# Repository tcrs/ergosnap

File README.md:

# ErgoSnap Keyboard

WARNING. This is rev1.1, which works fine but has a few issues:

 - The silkscreen for the ProMicro outline is incorrect for the USB-up placement
 - USB cable only just plugs into the ProMicro on the left half (plug shroud is
   against the edge of the PCB below the ProMicro)
 - SDA & SCL are the wrong way around on the 5pin header for the Pimoroni
   trackball breakout, so that doesn't work without some jumper wires...

[ErgoDash][1] layout with [Mitosis][2] style PCB construction, reversible ProMicro
chin from [Ergo42][3].

 - Removed all the wiring for backlight/underlight LEDs
 - Uses through-switch diode holes
 - M6 mouting holes on the "inside" board edges for tenting
 - 5 pin connector for [trackball module][4] (no software yet...)

[1]: https://github.com/omkbd/ErgoDash
[2]: https://github.com/reversebias/mitosis-hardware
[3]: https://github.com/Biacco42/Ergo42
[4]: https://shop.pimoroni.com/products/trackball-breakout

## Fabrication

I got my PCBS made at [JLCPCB][5]. No issues.

[5]: https://jlcpcb.com/

## BOM

 - 4 x PCBs
 - 68 x Keyswitches (Cherry MX or compatible)
 - 68 x Diodes (1N4148)
 - 2 x ProMicro + header pins 
 - 2 x TRRS jacks (PJ-320A [aliexpress](https://www.aliexpress.com/item/32825553898.html))
 - 1 x TRRS cable
 - 2 x 4k7 Ohm resistors (I2C pullups)
 - 2 x 5pin headers
 - 4 x M6 nylon screw thread + nuts (for tenting, optional)
 - Some sticky-backed neoprene tape (for padding/non-slip on the bottom of the
   board)

## Build

See [build guide](build_guide/).

## Software

[QMK](https://qmk.fm/). ErgoSnap uses exactly the same matrix as the ErgoDash,
so just build an ErgoDash layout (using the `LAYOUT_3key_1us` layout type).

For an example see my [`ergodash-isolike` layout](https://github.com/tcrs/qmk_firmware/tree/ergosnap-isolike).

Example make command:

	make ergodash/rev1:isolike:avrdude

## License

ErgoDash & Ergo42 are MIT, Mitosis is GPLv3. So this work as a whole is GPLv3.

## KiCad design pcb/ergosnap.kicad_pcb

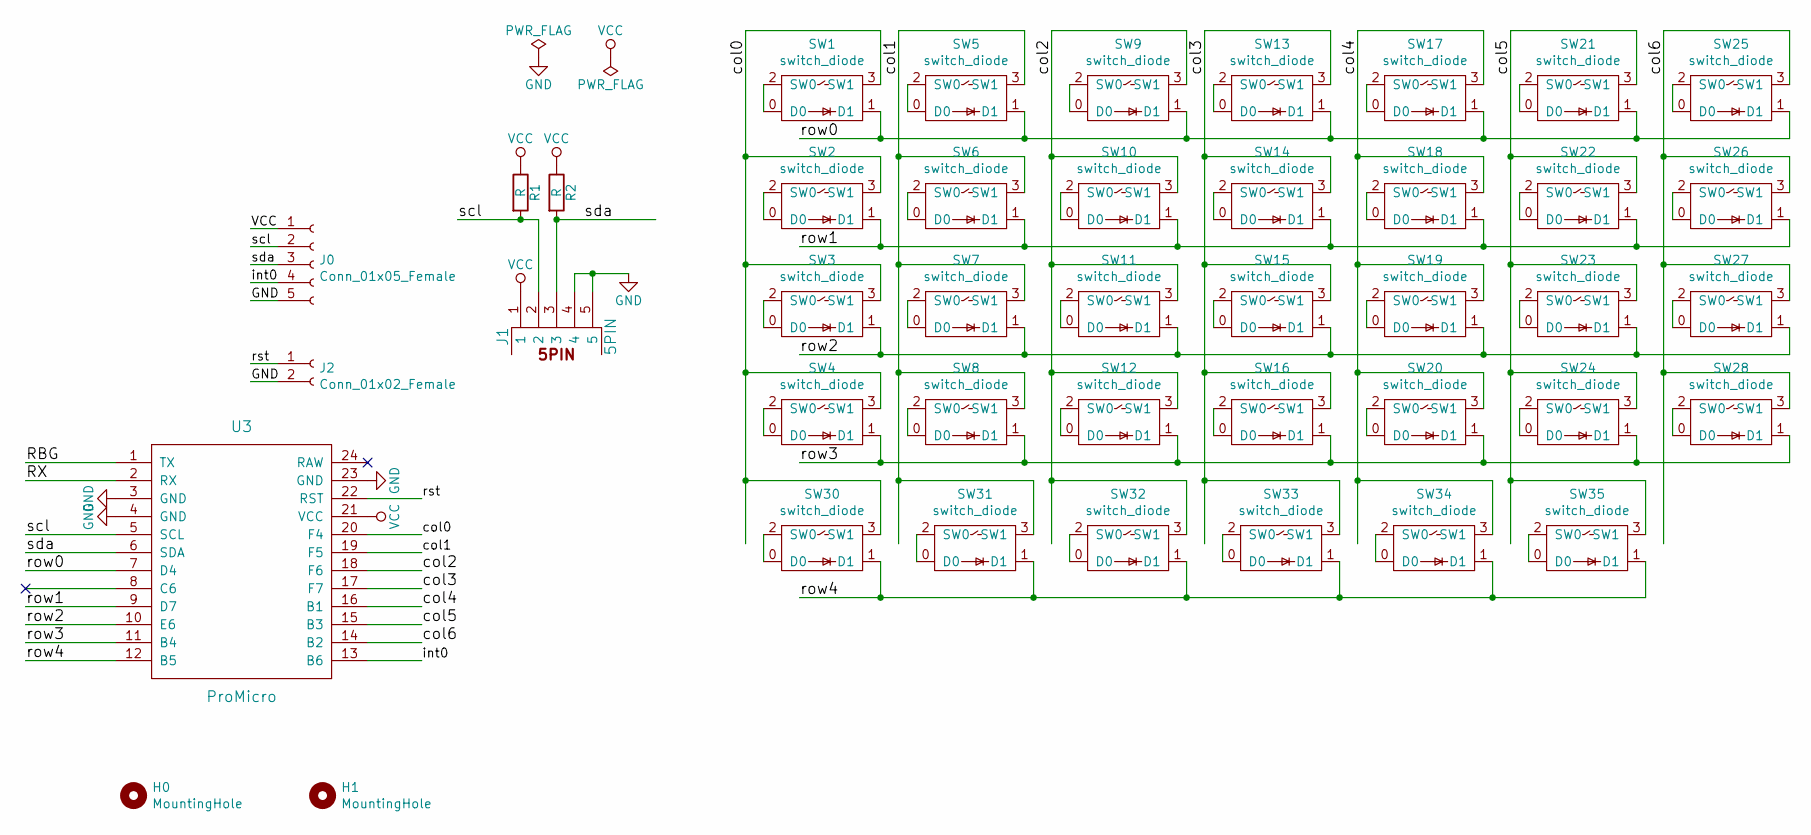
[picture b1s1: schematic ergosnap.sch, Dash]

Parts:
H0, H1: MountingHole; MountingHole_6.4mm_M6
J0: Conn_01x05_Female; pimoroni_trackball
J1: 5PIN; trrs_jack
J2: Conn_01x02_Female; SolderWirePad_1x02_P3.81mm_Drill0.8mm
R1, R2: R; R_Axial_DIN0207_L6.3mm_D2.5mm_P10.16mm_Horizontal
SW1, SW2, SW3, SW4, SW5, SW6, SW7, SW8, SW9, SW10, SW11, SW12, SW13, SW14, SW15, SW16, SW17, SW18, SW19, SW20, SW21, SW22, SW23, SW24, SW25, SW26, SW27, SW28, SW30, SW31, SW32, SW33, SW34, SW35: switch_diode; cherry_mx_diode_snapout
U3: ProMicro; ProMicroReversible

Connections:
/RBG: U3.1 (TX)
/RX: U3.2 (RX)
/col0: SW1.3 (SW1), SW2.3 (SW1), SW3.3 (SW1), SW4.3 (SW1), SW30.3 (SW1), U3.20 (F4)
/col1: SW5.3 (SW1), SW6.3 (SW1), SW7.3 (SW1), SW8.3 (SW1), SW31.3 (SW1), U3.19 (F5)
/col2: SW9.3 (SW1), SW10.3 (SW1), SW11.3 (SW1), SW12.3 (SW1), SW32.3 (SW1), U3.18 (F6)
/col3: SW13.3 (SW1), SW14.3 (SW1), SW15.3 (SW1), SW16.3 (SW1), SW33.3 (SW1), U3.17 (F7)
/col4: SW17.3 (SW1), SW18.3 (SW1), SW19.3 (SW1), SW20.3 (SW1), SW34.3 (SW1), U3.16 (B1)
/col5: SW21.3 (SW1), SW22.3 (SW1), SW23.3 (SW1), SW24.3 (SW1), SW35.3 (SW1), U3.15 (B3)
/col6: SW25.3 (SW1), SW26.3 (SW1), SW27.3 (SW1), SW28.3 (SW1), U3.14 (B2)
/int0: J0.4, U3.13 (B6)
/row0: SW1.1 (D1), SW5.1 (D1), SW9.1 (D1), SW13.1 (D1), SW17.1 (D1), SW21.1 (D1), SW25.1 (D1), U3.7 (D4)
/row1: SW2.1 (D1), SW6.1 (D1), SW10.1 (D1), SW14.1 (D1), SW18.1 (D1), SW22.1 (D1), SW26.1 (D1), U3.9 (D7)
/row2: SW3.1 (D1), SW7.1 (D1), SW11.1 (D1), SW15.1 (D1), SW19.1 (D1), SW23.1 (D1), SW27.1 (D1), U3.10 (E6)
/row3: SW4.1 (D1), SW8.1 (D1), SW12.1 (D1), SW16.1 (D1), SW20.1 (D1), SW24.1 (D1), SW28.1 (D1), U3.11 (B4)
/row4: SW30.1 (D1), SW31.1 (D1), SW32.1 (D1), SW33.1 (D1), SW34.1 (D1), SW35.1 (D1), U3.12 (B5)
/rst: J2.1, U3.22 (RST)
/scl: J0.2, J1.2, R1.2, U3.5 (SCL)
/sda: J0.3, J1.3, R2.2, U3.6 (SDA)
GND: J0.5, J1.4, J1.5, J2.2, U3.3 (GND), U3.4 (GND), U3.23 (GND)
unnamed: SW1.0 (D0), SW1.2 (SW0)
unnamed: SW2.0 (D0), SW2.2 (SW0)
unnamed: SW3.0 (D0), SW3.2 (SW0)
unnamed: SW4.0 (D0), SW4.2 (SW0)
unnamed: SW5.0 (D0), SW5.2 (SW0)
unnamed: SW6.0 (D0), SW6.2 (SW0)
unnamed: SW7.0 (D0), SW7.2 (SW0)
unnamed: SW8.0 (D0), SW8.2 (SW0)
unnamed: SW9.0 (D0), SW9.2 (SW0)
unnamed: SW10.0 (D0), SW10.2 (SW0)
unnamed: SW11.0 (D0), SW11.2 (SW0)
unnamed: SW12.0 (D0), SW12.2 (SW0)
unnamed: SW13.0 (D0), SW13.2 (SW0)
unnamed: SW14.0 (D0), SW14.2 (SW0)
unnamed: SW15.0 (D0), SW15.2 (SW0)
unnamed: SW16.0 (D0), SW16.2 (SW0)
unnamed: SW17.0 (D0), SW17.2 (SW0)
unnamed: SW18.0 (D0), SW18.2 (SW0)
unnamed: SW19.0 (D0), SW19.2 (SW0)
unnamed: SW20.0 (D0), SW20.2 (SW0)
unnamed: SW21.0 (D0), SW21.2 (SW0)
unnamed: SW22.0 (D0), SW22.2 (SW0)
unnamed: SW23.0 (D0), SW23.2 (SW0)
unnamed: SW24.0 (D0), SW24.2 (SW0)
unnamed: SW25.0 (D0), SW25.2 (SW0)
unnamed: SW26.0 (D0), SW26.2 (SW0)
unnamed: SW27.0 (D0), SW27.2 (SW0)
unnamed: SW28.0 (D0), SW28.2 (SW0)
unnamed: SW30.0 (D0), SW30.2 (SW0)
unnamed: SW31.0 (D0), SW31.2 (SW0)
unnamed: SW32.0 (D0), SW32.2 (SW0)
unnamed: SW33.0 (D0), SW33.2 (SW0)
unnamed: SW34.0 (D0), SW34.2 (SW0)
unnamed: SW35.0 (D0), SW35.2 (SW0)
VCC: J0.1, J1.1, R1.1, R2.1, U3.21 (VCC)

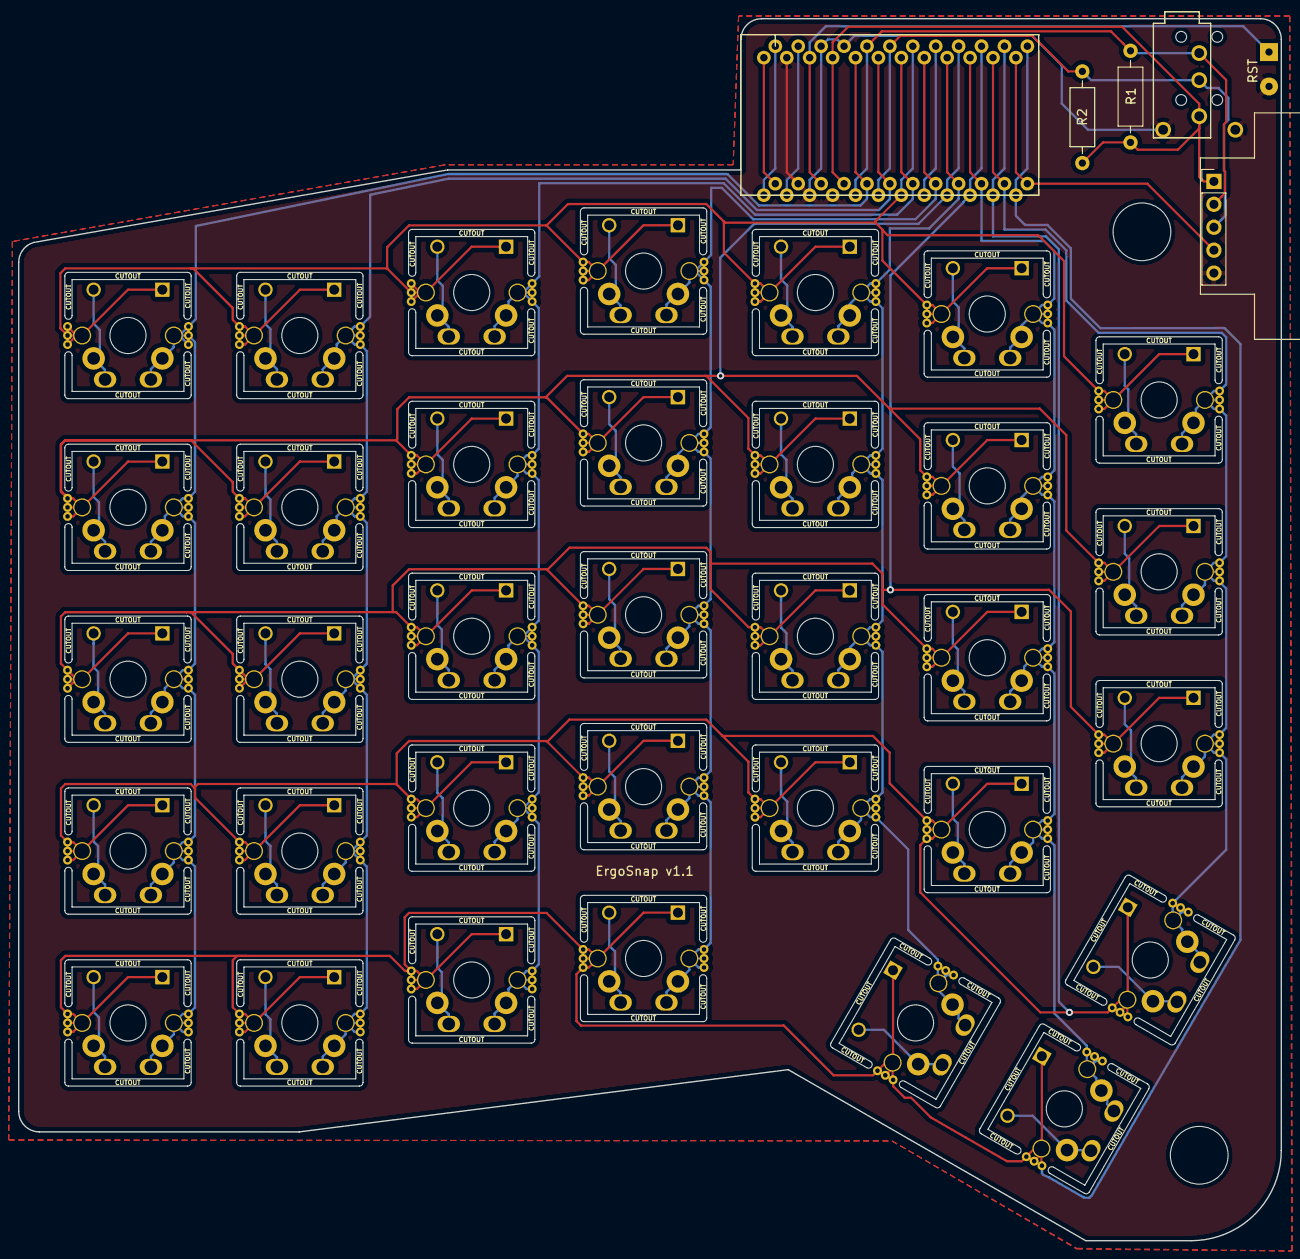
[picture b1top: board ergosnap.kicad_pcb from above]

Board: 2 copper layers, 140.0 x 135.5 mm, 42 parts (0 on the bottom side), 52 nets.

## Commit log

2019-07-08 Initial version of PCB
2019-07-08 Fiddle with trackball header
2019-07-09 Add cutout on silkscreen on slots
2019-07-09 Generated gerber files
2019-07-09 Add readme & license
2019-07-10 Actually add drill layer to gerber zip (oops)
2019-07-11 Remove alignment mark on Edge.Cuts layer
    Looks like JCLPCB treat this as part of the board
2019-07-12 Increase clearance between cutouts and board edge
    Went for around 5mm, JLCPCB want a minimum of 3mm
    Also rounded off the bottom right corner a bit more
2019-07-13 Tweak board outline a bit
    Right hand edge now a single line and actually straight
2019-07-15 Add more detail to readme
2019-07-25 Move diode holes to correct spacing
    Incorrectly measured this, diodes don't fit!
2019-07-27 Rev1.1 final (?)
    - Added reset header
    - Reshaped the bottom of the board slightly
    - Moved most of the component references off the silkscreen
    - Marked pin 1 in ProMicro footprint
    - Added 2 switch traces missed in last update
2019-08-16 Add build guide
2019-08-16 Add rev1.1 caveats to readme
2019-08-16 Add picture of final keyboard
2019-08-17 Add basic BOM & SW sections to readme
2021-03-31 Explain support for keyswitches without diode holes
    Can solder the diodes onto the bottom of the board to support switches
    without diode holes (e.g. Cherry MX).
